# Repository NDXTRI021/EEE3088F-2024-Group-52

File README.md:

# EEE3088F-2024-Group-52
 EEE3088F Project Repo for group 52. Subsections:
 1) Power - NDXTRI021 - Triss Naidoo
 2) Sensing - MPNMPU002 - Mpumelelo Mpanza

Production files can be found under {subsection}/jlcpcb/production_files

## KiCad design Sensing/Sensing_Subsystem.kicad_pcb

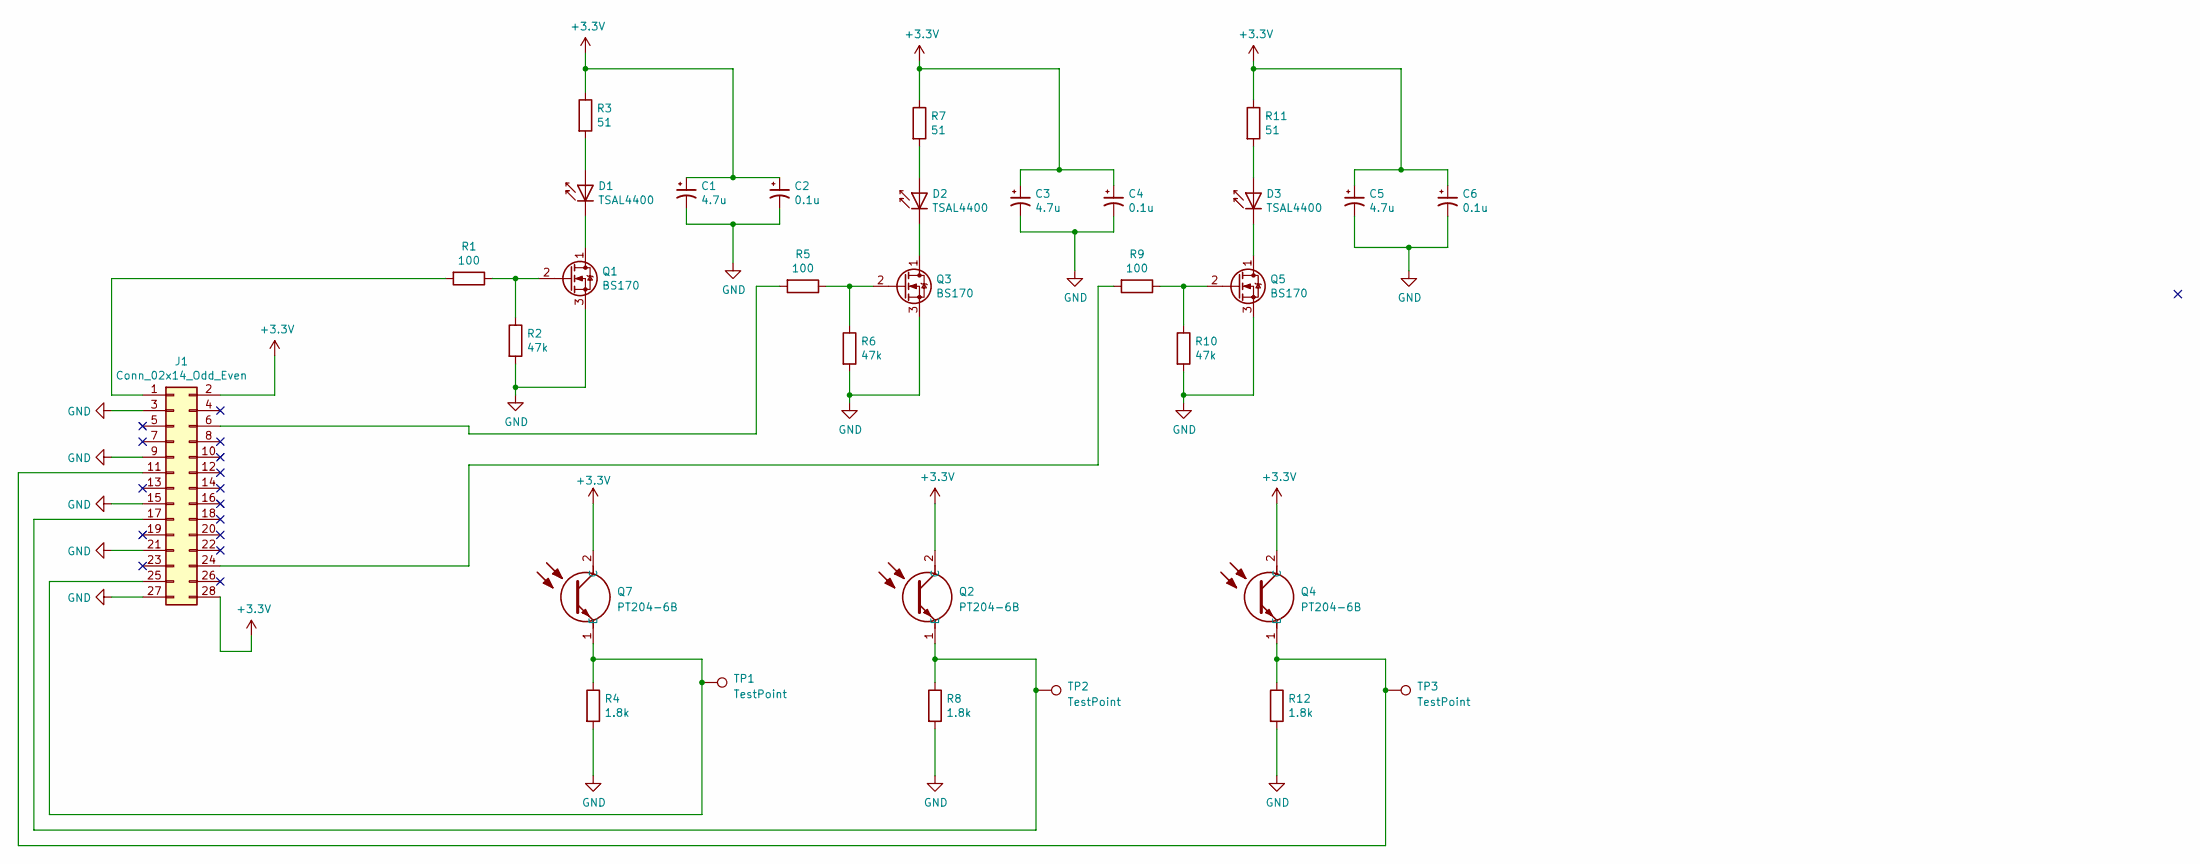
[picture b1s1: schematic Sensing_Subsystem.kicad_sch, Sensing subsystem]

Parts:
C1, C3, C5: 4.7u; CP_Elec_4x5.4
C2, C4, C6: 0.1u; CP_Elec_4x5.4
D1, D2, D3: TSAL4400; LED_D3.0mm_IRBlack
J1: Conn_02x14_Odd_Even; PinSocket_2x14_P2.54mm_Horizontal
Q1, Q3, Q5: BS170; TO-92_Inline
Q2, Q4, Q7: PT204-6B; PT2046B; Mouser Part Number N/A
R1, R5, R9: 100; R_0603_1608Metric
R2, R6, R10: 47k; R_0603_1608Metric
R3, R7, R11: 51; R_0603_1608Metric
R4, R8, R12: 1.8k; R_0603_1608Metric
TP1, TP2, TP3: TestPoint; TestPoint_Pad_1.0x1.0mm

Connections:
+3V3: C1.1, C2.1, C3.1, C4.1, C5.1, C6.1, J1.2, J1.28, Q2.2 (C), Q4.2 (C), Q7.2 (C), R3.1, R7.1, R11.1
GND: C1.2, C2.2, C3.2, C4.2, C5.2, C6.2, J1.3, J1.9, J1.15, J1.21, J1.27, Q1.3 (S), Q3.3 (S), Q5.3 (S), R2.2, R4.2, R6.2, R8.2, R10.2, R12.2
unnamed: D1.2 (A), R3.2
unnamed: D1.1 (K), Q1.1 (D)
unnamed: D2.2 (A), R7.2
unnamed: D2.1 (K), Q3.1 (D)
unnamed: D3.2 (A), R11.2
unnamed: D3.1 (K), Q5.1 (D)
unnamed: J1.1, R1.2
unnamed: J1.6, R5.2
unnamed: J1.11, Q4.1 (E), R12.1, TP3.1
unnamed: J1.17, Q2.1 (E), R8.1, TP2.1
unnamed: J1.24, R9.2
unnamed: J1.25, Q7.1 (E), R4.1, TP1.1
unnamed: Q1.2 (G), R1.1, R2.1
unnamed: Q3.2 (G), R5.1, R6.1
unnamed: Q5.2 (G), R9.1, R10.1

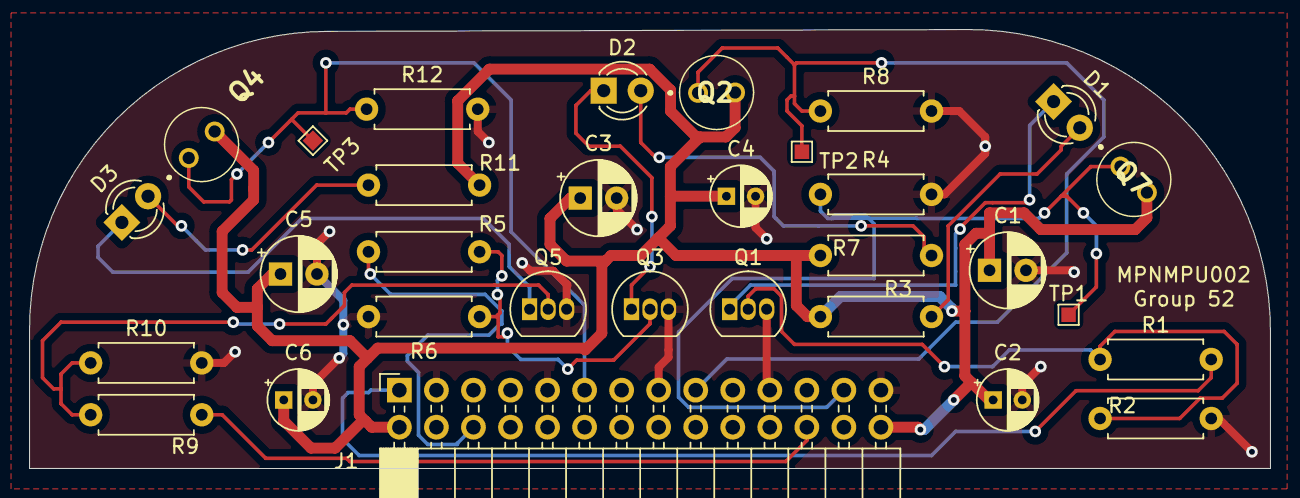
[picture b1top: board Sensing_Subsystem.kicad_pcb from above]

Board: 2 copper layers, 85.1 x 30.1 mm, 31 parts (0 on the bottom side), 17 nets.

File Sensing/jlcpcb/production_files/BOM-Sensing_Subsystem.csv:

Comment,Designator,Footprint,LCSC
BS170,"Q1,Q3,Q5",TO-92_Inline,C111691
4.7u,"C1,C3,C5",CP_Elec_4x5.4,C116399
100,"R1,R5,R9",R_0603_1608Metric,C22775
51,"R11,R3,R7",R_0603_1608Metric,C23197
47k,"R10,R2,R6",R_0603_1608Metric,C25819
0.1u,"C2,C4,C6",CP_Elec_4x5.4,C271438
1.8k,"R12,R4,R8",R_0603_1608Metric,C4177
PT204-6B,"Q2,Q4,Q7",PT2046B,C5133
TSAL4400,"D1,D2,D3",LED_D3.0mm_IRBlack,C94135
TestPoint,TP1,TestPoint_Pad_1.0x1.0mm,
TestPoint,TP3,TestPoint_Pad_1.0x1.0mm,
Conn_02x14_Odd_Even,J1,PinSocket_2x14_P2.54mm_Horizontal,
TestPoint,TP2,TestPoint_Pad_1.0x1.0mm,

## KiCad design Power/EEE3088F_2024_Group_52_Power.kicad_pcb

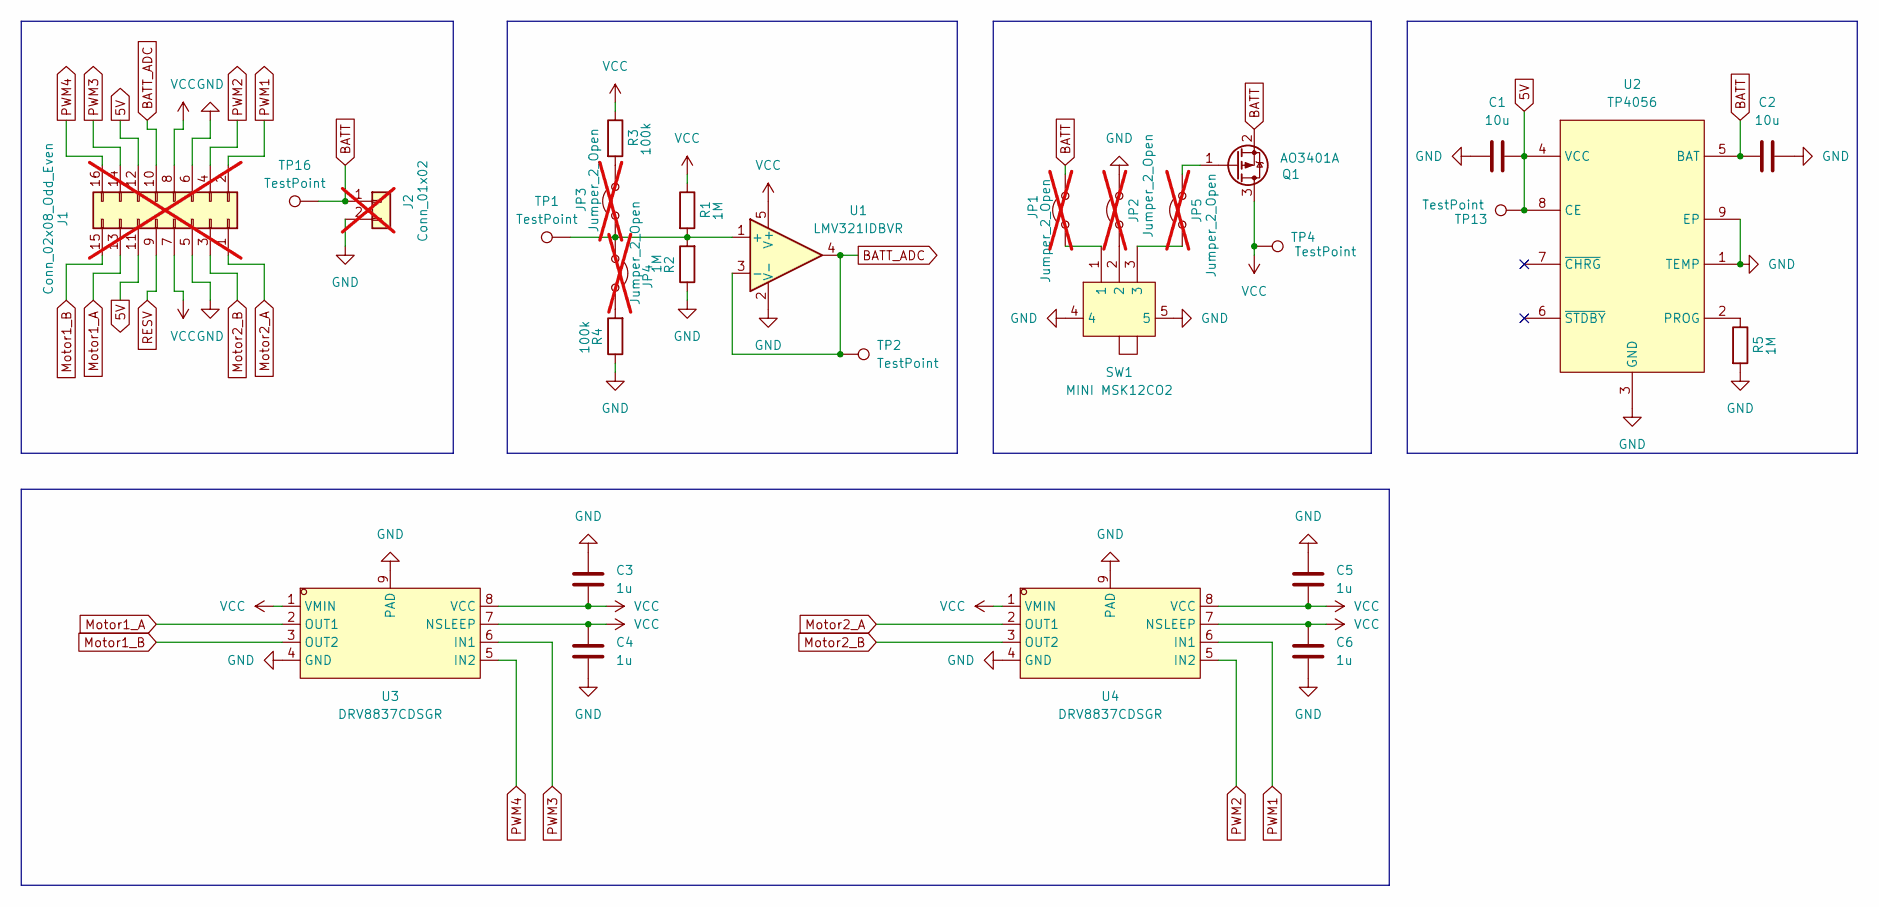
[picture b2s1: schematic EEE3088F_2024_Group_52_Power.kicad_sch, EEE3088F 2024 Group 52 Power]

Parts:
C1, C2: 10u; C_0603_1608Metric
C3, C4, C5, C6: 1u; C_0603_1608Metric
J1: Conn_02x08_Odd_Even; PinHeader_2x08_P2.54mm_Vertical; not fitted
J2: Conn_01x02; JST_PH_S2B-PH-K_1x02_P2.00mm_Horizontal; not fitted
JP1, JP2, JP3, JP4, JP5: Jumper_2_Open; SolderJumper-3_P1.3mm_Open_Pad1.0x1.5mm_NumberLabels; not fitted
Q1: AO3401A; SOT-23_L2.9-W1.3-P1.90-LS2.4-BR
R1, R2, R5: 1M; R_0603_1608Metric
R3, R4: 100k; R_0603_1608Metric
SW1: MINI MSK12CO2; SW-SMD_MSK12CO2; LCSC Part C2681570
TP1, TP2, TP4, TP13, TP16: TestPoint; TestPoint_THTPad_D1.5mm_Drill0.7mm
U1: LMV321IDBVR; SOT-23-5_L3.0-W1.7-P0.95-LS2.8-BR
U2: TP4056; ESOP-8_L4.9-W3.9-P1.27-LS6.0-BL-EP; LCSC Part C16581
U3, U4: DRV8837CDSGR; WSON-8_L2.0-W2.0-P0.50-TL-EP; LCSC Part C191000

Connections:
5V: C1.2, J1.11, J1.12, TP13.1, U2.4 (VCC), U2.8 (CE)
BATT: C2.1, J2.1, JP1.2 (B), Q1.2 (S), TP16.1, U2.5 (BAT)
BATT_ADC: J1.10, TP2.1, U1.3 (-), U1.4
GND: C1.1, C2.2, C3.2, C4.2, C5.2, C6.2, J1.5, J1.6, J2.2, JP2.2 (B), R2.1, R4.1, R5.2, SW1.4, SW1.5, U1.2 (V-), U2.1 (TEMP), U2.3 (GND), U2.9 (EP), U3.4 (GND), U3.9 (PAD), U4.4 (GND), U4.9 (PAD)
Motor1_A: J1.13, U3.2 (OUT1)
Motor1_B: J1.15, U3.3 (OUT2)
Motor2_A: J1.1, U4.2 (OUT1)
Motor2_B: J1.3, U4.3 (OUT2)
unnamed: JP1.1 (A), SW1.1
unnamed: JP2.1 (A), SW1.2
unnamed: JP3.1 (A), JP4.1 (A), R1.2, R2.2, TP1.1, U1.1 (+)
unnamed: JP3.2 (B), R3.2
unnamed: JP4.2 (B), R4.2
unnamed: JP5.1 (A), SW1.3
unnamed: JP5.2 (B), Q1.1 (G)
unnamed: R5.1, U2.2 (PROG)
PWM1: J1.2, U4.6 (IN1)
PWM2: J1.4, U4.5 (IN2)
PWM3: J1.14, U3.6 (IN1)
PWM4: J1.16, U3.5 (IN2)
RESV: J1.9
VCC: C3.1, C4.1, C5.1, C6.1, J1.7, J1.8, Q1.3 (D), R1.1, R3.1, TP4.1, U1.5 (V+), U3.1 (VMIN), U3.7 (NSLEEP), U3.8 (VCC), U4.1 (VMIN), U4.7 (NSLEEP), U4.8 (VCC)

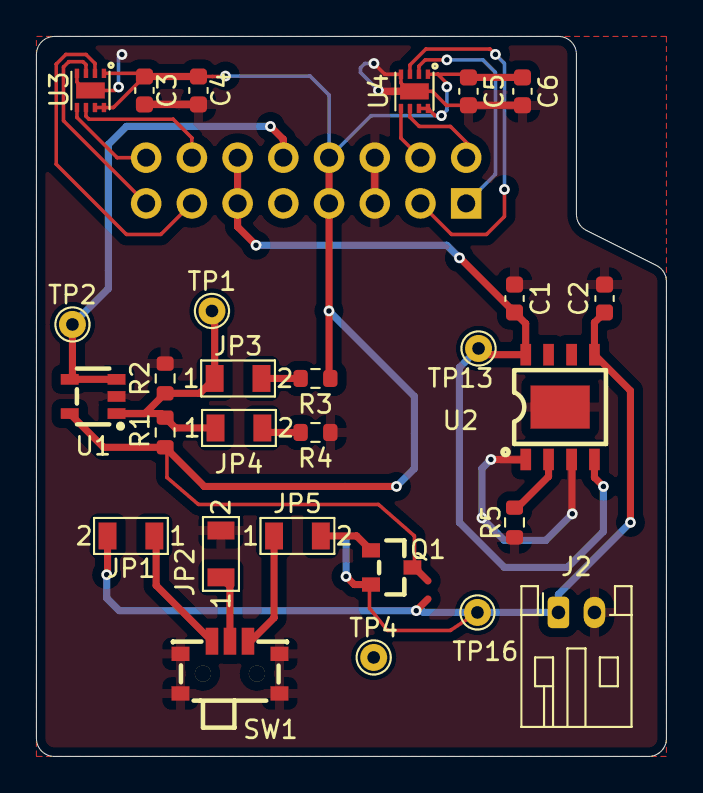
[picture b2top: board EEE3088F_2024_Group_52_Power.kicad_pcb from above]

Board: 2 copper layers, 35.0 x 40.0 mm, 29 parts (1 on the bottom side), 21 nets.

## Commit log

2024-03-18 Update README.md
    Updated README file
2024-03-20 Create EEE3088F_Motor_Driver_Simulation.asc
    ADDED simulation of proposed motor driver circuit.
2024-03-21 Modified simulation file
2024-03-24 Finalised rev0 PCB and schematics, included gerber
2024-03-24 Moved power to own folder
2024-03-25 Proposed fixes to power PCB flaws
2024-04-18 misc changes
2024-04-18 Revert "pull from main init"
2024-04-18 Sensing subsection uploaded. Misc files deleted
